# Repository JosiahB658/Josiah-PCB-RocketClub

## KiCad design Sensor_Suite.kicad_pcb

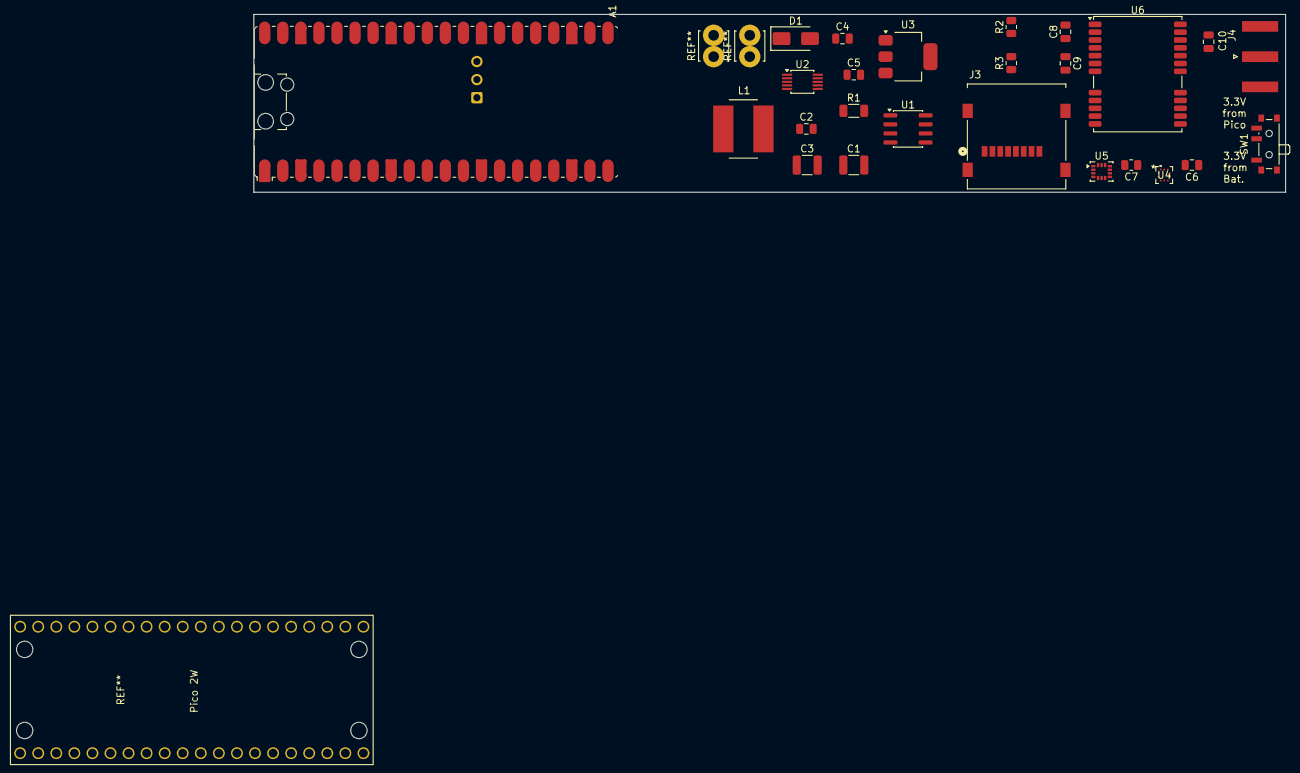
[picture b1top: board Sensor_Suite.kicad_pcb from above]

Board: 4 copper layers, 145.1 x 25.0 mm, 25 parts (0 on the bottom side), 13 nets.

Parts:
A1: RaspberryPi_Pico_W; RaspberryPi_Pico_W_SMD_HandSolder
C1: 100 uF; C_1210_3225Metric
C2, C6, C9, C10: 0.1 uF; C_0805_2012Metric
C3: 100uF; C_1210_3225Metric
C4, C5, C8: 10 uF; C_0805_2012Metric
C7: 0.1 uF; R_0805_2012Metric
D1: SS34; D_SMA
J3: 472192001; CONN_47219-2001_MOL
J4: SMA-KE-Z; SMA_Amphenol_132289_EdgeMount
L1: 47 uH; L_Bourns_SRN8040TA
R1: 10mOhm; R_1206_3216Metric
R2, R3: 4.7 kOhm; R_0805_2012Metric
SW1: SW_SPDT; SW_SPDT_PCM12
U1: XL1509-5.0; SOIC-8_3.9x4.9mm_P1.27mm
U2: INA226; TSSOP-10_3x3mm_P0.5mm
U3: AMS1117-3.3; SOT-223-3_TabPin2
U4: BMP581; QFN10_BMP581_BOS
U5: LSM6DS3; LGA-14_3x2.5mm_P0.5mm_LayoutBorder3x4y
U6: NEO-M9N; ublox_NEO

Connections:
+3.3V: C2.1, C6.1, C7.1, C8.1, C9.1, C10.1, J3.4, R2.1, R3.1, SW1.2 (B), U2.6 (VS), U4.1 (VDDIO), U4.10 (VDD), U5.1 (SDO/SA0), U5.5 (VDDIO), U5.8 (VDD), U6.7 (VDD_USB), U6.9 (VCC_RF), U6.22 (V_BCKP), U6.23 (VCC)
/3.3V: A1.37 (3V3_EN), SW1.3 (C)
/5V: A1.39 (VSYS), C3.1, C4.2, D1.1 (K), L1.1, L1.2, R1.1, R1.2, U1.2 (OUT), U1.3 (FB), U2.8 (Vbus), U2.9 (Vin-), U2.10 (Vin+), U3.3 (VI)
/CS: A1.22 (GPIO17), J3.2
/MISO: A1.21 (GPIO16), J3.7
/MOSI: A1.25 (GPIO19), J3.3
/PWR in: C1.1, U1.1 (VIN)
/SCL/SCK line: A1.20 (GPIO15), R3.2, U2.5 (SCL), U4.2 (SCK), U5.13 (SCL), U6.19 (SCL/SPI_CLK)
/SDA/SDI line: A1.19 (GPIO14), R2.2, U2.4 (SDA), U4.4 (SDI), U5.14 (SDA), U6.18 (SDA/~SPI_CS)
/SLK: A1.24 (GPIO18), J3.5
GND: A1.3 (GND), A1.8 (GND), A1.13 (GND), A1.18 (GND), A1.23 (GND), A1.28 (GND), A1.38 (GND), C1.2, C2.2, C3.2, C4.1, C5.2, C6.2, C7.2, C8.2, C9.2, C10.2, D1.2 (A), J3.6, J4.2 (Ext), U1.4 (~EN), U1.5 (GND), U1.6 (GND), U1.7 (GND), U1.8 (GND), U2.1 (A1), U2.2 (A0), U2.7 (GND), U3.1 (GND), U4.3 (VSS), U4.5 (SDO), U4.8 (VSS), U4.9 (VSS), U5.6 (GND), U5.7 (GND), U6.10 (GND), U6.12 (GND), U6.13 (GND), U6.24 (GND)
unnamed: J4.1 (In), U6.11 (RF_IN)
unnamed: C5.1, SW1.1 (A), U3.2 (VO)
